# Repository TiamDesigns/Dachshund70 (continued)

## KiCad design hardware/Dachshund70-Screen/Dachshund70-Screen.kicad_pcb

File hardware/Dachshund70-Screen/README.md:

# Dachshund70 screen board

Rev 3.0 (2026-11-17). The board under the 2.7" Sharp memory LCD: the panel's socket, its 5 V supply and the
five layer and battery LEDs. It joins the mainboard with one 12-way flat cable. KiCad 10 project, 2 layers,
0.8 mm FR4, 40.0 × 47.0 mm (x 309 to 349, y 88 to 135 KiCad mm) with R1 corners.

Why a separate board again: the mainboard is held by the switches and moves with the plate's flex, and the
screen is fixed in the case. From mainboard rev 1.3 the mainboard keeps only the keys, the MCU, power and the
connectors, so the same mainboard can go into a cheaper Dachshund70 Lite with no screen and no encoder.

- **Panel:** Sharp LS027B7DH01 (400 × 240, 2.7", 62.8 × 42.82 × 1.64 mm glass, 58.8 × 35.28 mm picture). It
  stands on end beside the knob, so the picture is 240 × 400 in portrait. The firmware build is
  `-DEXTRA_DTC_OVERLAY_FILE=displays/sharp-ls027b7dh01-portrait.overlay`.
- **Every part is on the bottom side.** The top side is a plain ground pour, taped to the back of the panel;
  the LEDs shine up through cut-outs in the board (reverse mount).
- **Same coordinates as the mainboard.** The board is drawn where it sits in the case, so its STEP drops into
  the case model at the same x and y (`python hardware/export_step.py`).

Rev 1.0 (PR #83) drove the 2.13" e-paper; rev 2.0 (PR #84) was this panel without the LEDs; PR #85 moved the
circuit onto the mainboard (rev 1.2), which rev 1.3 undoes.

## Circuit

- **5 V supply.** The panel runs from 5 V. U1, a TI TPS61222 (fixed 5 V boost), makes it from the mainboard's
  3V3, with L1 (4.7 µH), C1 (10 µF in) and C2 (10 µF out).
- **Enable.** U1's EN is VLCD_EN, from the MCU's P0.24 (the overlays' BUSY), with R1 (100 kΩ) pulling it up,
  so the 5 V is on unless the firmware drives it low.
- **Logic.** 3.3 V logic straight into the panel. EXTMODE is tied high, so VCOM follows EXTCOMIN (1 Hz).
- **Sharp's capacitors.** C3 (1 µF), C4 and C5 (100 nF), close to J1.
- **LEDs.** D1 (layer) and D2 to D5 (battery gauge 25/50/75/100%), SK6812MINI-E reverse mount at 7.5 mm pitch
  in a row at y 130.5, x 314.56 to 344.56, each with a 100 nF cap (C6 to C10). They are LEDs 1 to 5 of the
  chain: the data comes from the Caps Lock LED (D2 on the mainboard, LED 0) on the cable as LED_DIN. LED_VDD is
  the mainboard's switched LED supply (its load switch and level buffer stay on the mainboard).

## Cable

Mainboard J4 and this board's J2 are both Hirose FH12-12S-0.5SH(55) (12-way, 0.5 mm). From mainboard rev 1.4 both
sit on the **bottom** of their boards, so JLC can assemble each board from one side. J4 is at the mainboard's right
edge, mouth +x, pads at x 319.45, y 115.15 (pin 1) to 120.65 (pin 12). J2 is 6 mm further right (pads at x 325.45)
at the same y, also mouth +x. The cable leaves J4, loops up and back into J2: a C-shaped loop past the mainboard's
right edge (x 326).

- Use a **0.5 mm pitch, 12-way FFC with contacts on opposite sides at the two ends** (type B): both connectors
  hang under their boards, and the loop turns the cable over. Each conductor keeps its y, so **J2 pin n = J4
  pin n**. The schematics already account for that.
- Length: set it from the case model (gap between the boards plus the loop), and buy a few lengths around it.

| J4 pin (mainboard) | Mainboard net | MCU pin | J2 pin (screen) | Screen net | Panel pin |
| --- | --- | --- | --- | --- | --- |
| 1, 2 | LED_VDD | | 1, 2 | LED_VDD | |
| 3 | GND | | 3 | GND | 9, 10 |
| 4 | LED_DOUT (from D2) | (P0.06 via D2) | 4 | LED_DIN | |
| 5 | GND | | 5 | GND | |
| 6 | DISP_CLK | P0.19 | 6 | SCLK | 1 |
| 7 | DISP_DIN | P0.21 | 7 | SI | 2 |
| 8 | DISP_CS | P0.20 | 8 | SCS (active high) | 3 |
| 9 | DISP_DC | P0.23 | 9 | EXTCOMIN | 4 |
| 10 | DISP_RST | P0.22 | 10 | DISP | 5 |
| 11 | DISP_BUSY | P0.24 | 11 | VLCD_EN (U1's EN) | |
| 12 | +3V3 | | 12 | +3V3 (U1 input) | |

Panel pins 6, 7 (VDDA, VDD) and 8 (EXTMODE) are on +5V. Without the screen board (the Lite), J4 can be left
unfitted: Caps Lock still works, and the firmware is built without a display overlay.

## Geometry

- **J1** (panel socket, FH12-10S) is at (314.6, 110.6), mouth −x, pads at x 316.45 from pin 10 (y 108.35) to
  pin 1 (y 112.85). **J1 pin n = panel pin 11 − n**, assuming the tail folds back under the glass's left edge
  with pin 1 at the top (check it, below).
- The boost (U1, L1, C1, C2, R1) is at the top right, around (330, 96).
- The board stays inside the glass (about x 308 to 351, y 63 to 126) except its LED row, which sits below the
  glass at y 130.5, where the five LEDs light the case's holes.

## Routing

Autorouted with Freerouting 1.9 around a hand-routed LED chain, then hand-fixed (2026-11-18, rev 3.1). The routes
are in `screen_routes.py` (`ROUTES`, `VIAS`), which `gen_screen.py` reads. Power (+5V, +3V3, LED_VDD) and signals
are 0.2 mm (the FH12's 0.5 mm pitch leaves no room for wider tracks at its pads), ground links 0.25 mm; vias
0.6/0.3 mm. The LED chain runs its data on the front between LEDs and LED_VDD as one front row at y 123.8, so the
back stays free around the LEDs' ground pads. There is no ground pour over the mainboard's antenna (rule area
x 318-332, y 120-135, "over the mainboard antenna"): the ground pads of D2, D3, C7, C8 and J2's lower tab reach the
pour on short tracks. There is no stitching grid: eight ground vias, by the connectors, the boost and the LEDs, join
the two pours (and the pour boxed in by J1's tracks); 0.5 mm keep-outs run along the edges and ±2 mm around each LED cut-out
(`Dachshund70-Screen.kicad_dru` allows 0.3 mm from the cut-outs).

## Status

Checked in KiCad only; nothing is ordered, made or fitted. ERC: 0. DRC with schematic parity and every severity:
0 violations, 0 unconnected items.

## Open checks before ordering

- **Panel FPC: pin 1, contact face, pitch, tail position and length**, from Sharp's Figure 8-1 or a panel in
  hand. If pin 1 lands at the bottom of J1, swap `SOCKET` in `gen_screen.py` and reroute.
- **FFC contact sides**: with a type-B cable in a C loop, J4 and J2 (both on the bottom of their boards) must
  each face the cable's contacts.
- **LCSC numbers:** J1/J2 (FH12-10S, FH12-12S), U1 (TPS61222DCKR) and L1 (FNR3015S4R7MT) are still blank.
- **Case:** the board pocket, the cable loop past the mainboard's right edge and the LED holes at x 314.56 +
  7.5 i, y 130.5.

## Regenerating

Run with KiCad 10's Python, from the repo root:

```
"C:/Program Files/KiCad/10.0/bin/python.exe" hardware/Dachshund70-Screen/gen_screen.py
```

This rewrites the schematic and the whole board: placement, the routes from `screen_routes.py`, and the filled
pours. Then check it:

```
kicad-cli pcb drc --schematic-parity --severity-all Dachshund70-Screen.kicad_pcb
kicad-cli sch erc --severity-all Dachshund70-Screen.kicad_sch
```

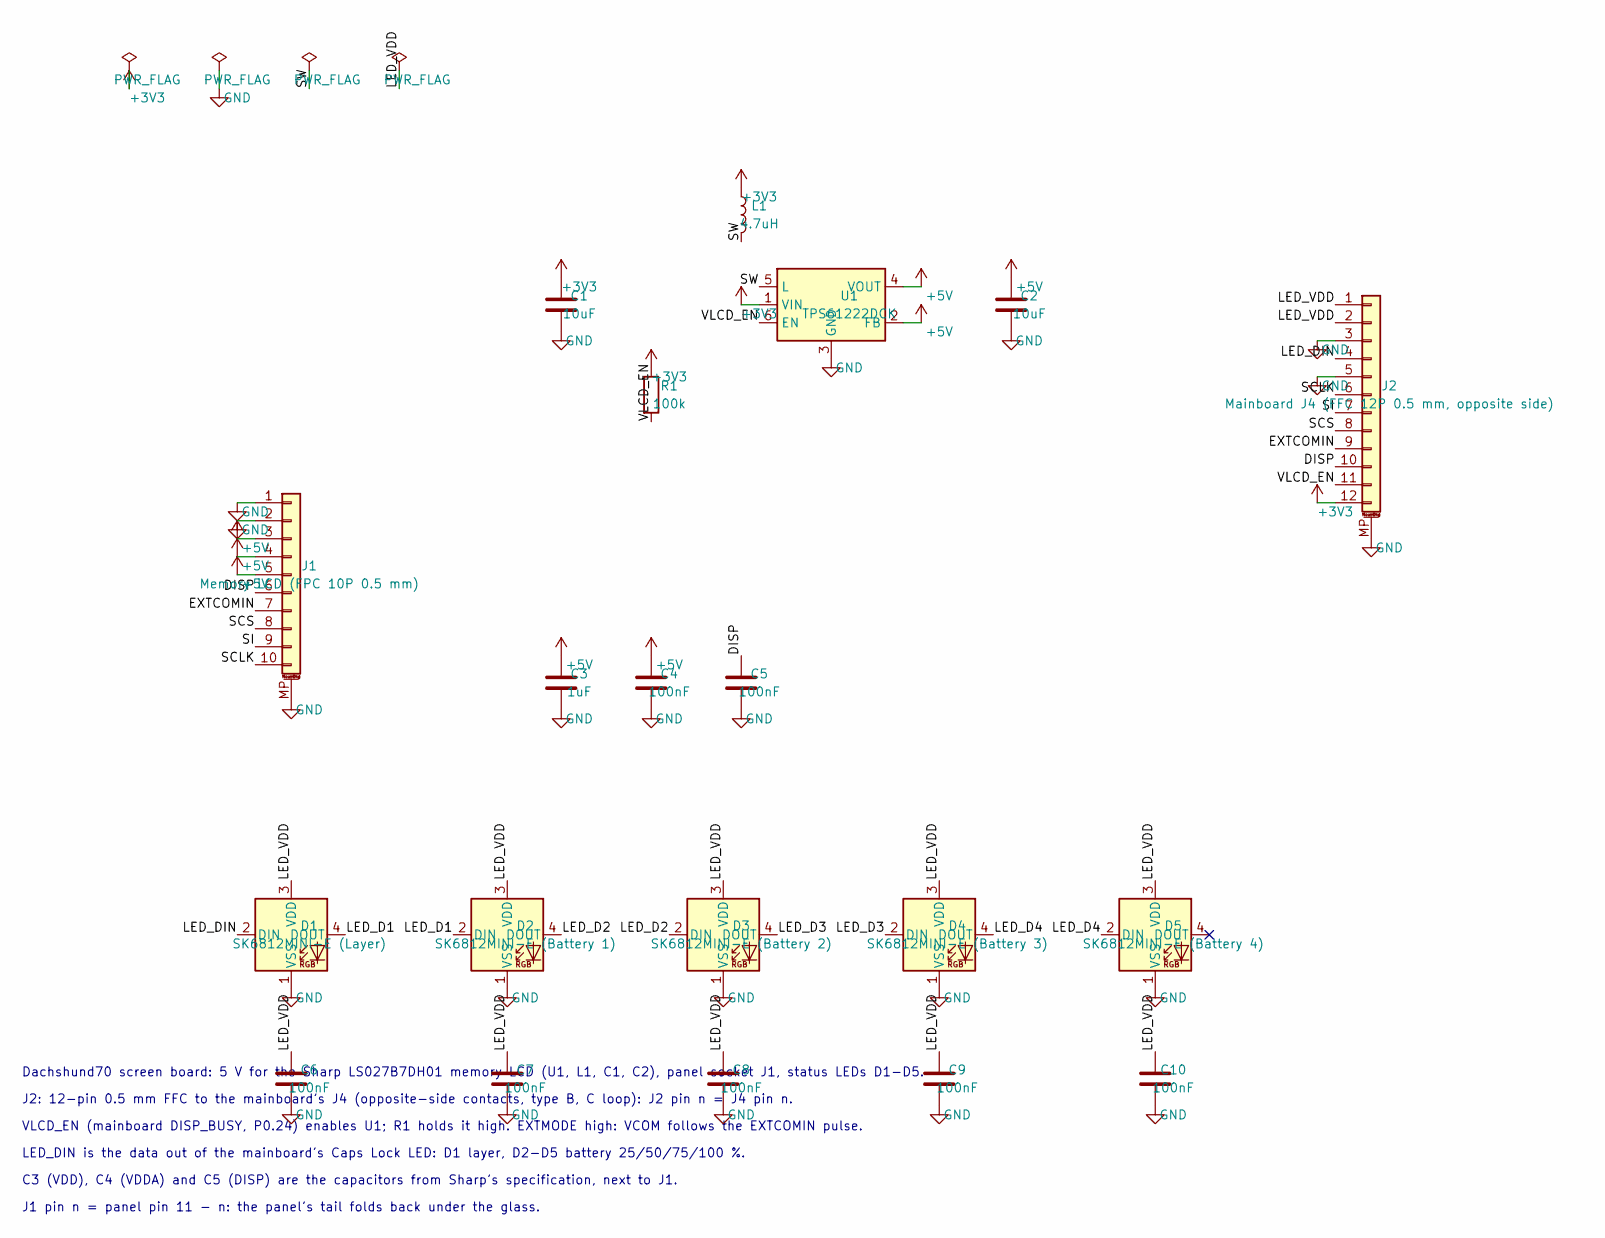
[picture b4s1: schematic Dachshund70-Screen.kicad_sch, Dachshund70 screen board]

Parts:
C1, C2: 10uF; C_0603_1608Metric; MPN Samsung CL10A106KP8NNNC (10 uF, 10 V, X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; LCSC C19702
C3: 1uF; C_0402_1005Metric; MPN Samsung CL05A105KA5NQNC (1 uF, 25 V, X5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; LCSC C52923
C4, C5, C6, C7, C8, C9, C10: 100nF; C_0402_1005Metric; MPN Samsung CL05B104KO5NNNC; LCSC C1525
D1: SK6812MINI-E (Layer); LED_SK6812MINI-E_3.2x2.8mm_P1.5mm_ReverseMount_Cutout3.4; MPN OPSCO SK6812MINI-E; LCSC C5149201
D2: SK6812MINI-E (Battery 1); LED_SK6812MINI-E_3.2x2.8mm_P1.5mm_ReverseMount_Cutout3.4; MPN OPSCO SK6812MINI-E; LCSC C5149201
D3: SK6812MINI-E (Battery 2); LED_SK6812MINI-E_3.2x2.8mm_P1.5mm_ReverseMount_Cutout3.4; MPN OPSCO SK6812MINI-E; LCSC C5149201
D4: SK6812MINI-E (Battery 3); LED_SK6812MINI-E_3.2x2.8mm_P1.5mm_ReverseMount_Cutout3.4; MPN OPSCO SK6812MINI-E; LCSC C5149201
D5: SK6812MINI-E (Battery 4); LED_SK6812MINI-E_3.2x2.8mm_P1.5mm_ReverseMount_Cutout3.4; MPN OPSCO SK6812MINI-E; LCSC C5149201
J1: Memory LCD (FPC 10P 0.5 mm); Hirose_FH12-10S-0.5SH_1x10-1MP_P0.50mm_Horizontal; MPN Hirose FH12-10S-0.5SH(55)
J2: Mainboard J4 (FFC 12P 0.5 mm, opposite side); Hirose_FH12-12S-0.5SH_1x12-1MP_P0.50mm_Horizontal; MPN Hirose FH12-12S-0.5SH(55)
L1: 4.7uH; L_Changjiang_FNR3015S; MPN Changjiang FNR3015S4R7MT (4.7 uH, 3 x 3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
R1: 100k; R_0402_1005Metric; MPN UNI-ROYAL 0402WGF1003TCE; LCSC C25741
U1: TPS61222DCK; SOT-363_SC-70-6; MPN TI TPS61222DCKR (5 V boost)

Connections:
+3V3: C1.1, J2.12, L1.1, R1.1, U1.1 (VIN)
+5V: C2.1, C3.1, C4.1, J1.3, J1.4, J1.5, U1.2 (FB), U1.4 (VOUT)
/DISP: C5.1, J1.6, J2.10
/EXTCOMIN: J1.7, J2.9
/LED_D1: D1.4 (DOUT), D2.2 (DIN)
/LED_D2: D2.4 (DOUT), D3.2 (DIN)
/LED_D3: D3.4 (DOUT), D4.2 (DIN)
/LED_D4: D4.4 (DOUT), D5.2 (DIN)
/LED_DIN: D1.2 (DIN), J2.4
/LED_VDD: C6.1, C7.1, C8.1, C9.1, C10.1, D1.3 (VDD), D2.3 (VDD), D3.3 (VDD), D4.3 (VDD), D5.3 (VDD), J2.1, J2.2
/SCLK: J1.10, J2.6
/SCS: J1.8, J2.8
/SI: J1.9, J2.7
/SW: L1.2, U1.5 (L)
/VLCD_EN: J2.11, R1.2, U1.6 (EN)
GND: C1.2, C2.2, C3.2, C4.2, C5.2, C6.2, C7.2, C8.2, C9.2, C10.2, D1.1 (VSS), D2.1 (VSS), D3.1 (VSS), D4.1 (VSS), D5.1 (VSS), J1.1, J1.2, J1.MP (MountPin), J2.3, J2.5, J2.MP (MountPin), U1.3 (GND)

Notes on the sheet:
Dachshund70 screen board: 5 V for the Sharp LS027B7DH01 memory LCD (U1, L1, C1, C2), panel socket J1, status LEDs D1-D5.
J2: 12-pin 0.5 mm FFC to the mainboard's J4 (opposite-side contacts, type B, C loop): J2 pin n = J4 pin n.
VLCD_EN (mainboard DISP_BUSY, P0.24) enables U1; R1 holds it high. EXTMODE high: VCOM follows the EXTCOMIN pulse.
LED_DIN is the data out of the mainboard's Caps Lock LED: D1 layer, D2-D5 battery 25/50/75/100 %.
C3 (VDD), C4 (VDDA) and C5 (DISP) are the capacitors from Sharp's specification, next to J1.
J1 pin n = panel pin 11 - n: the panel's tail folds back under the glass.

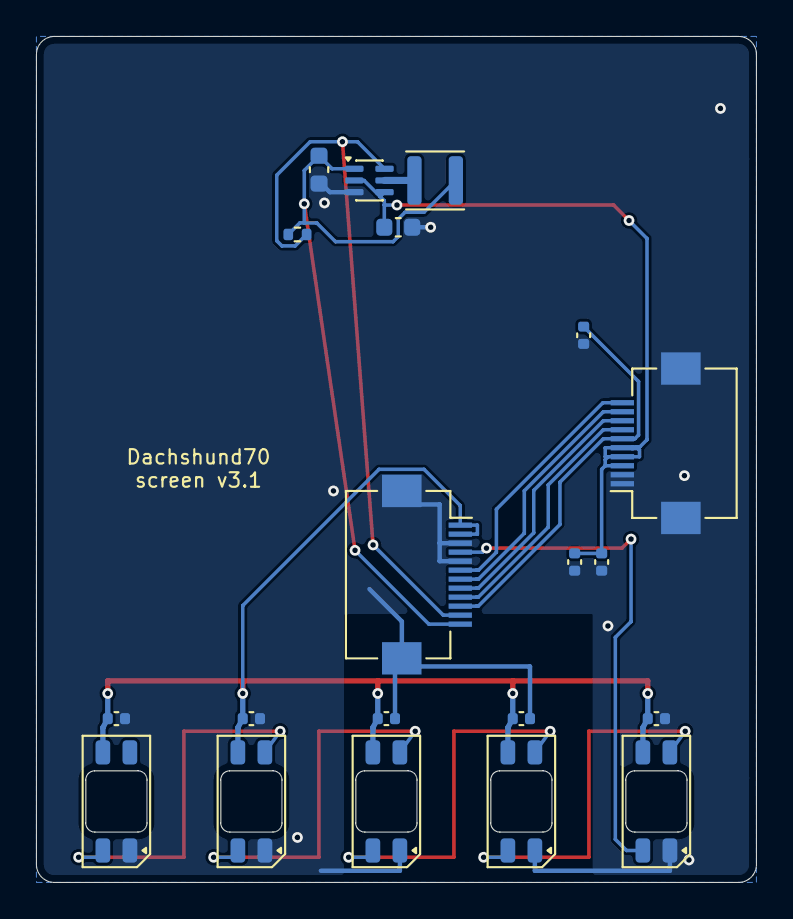
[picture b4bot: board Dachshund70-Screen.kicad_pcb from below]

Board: 2 copper layers, 40.0 x 47.0 mm, 20 parts (20 on the bottom side), 16 nets.

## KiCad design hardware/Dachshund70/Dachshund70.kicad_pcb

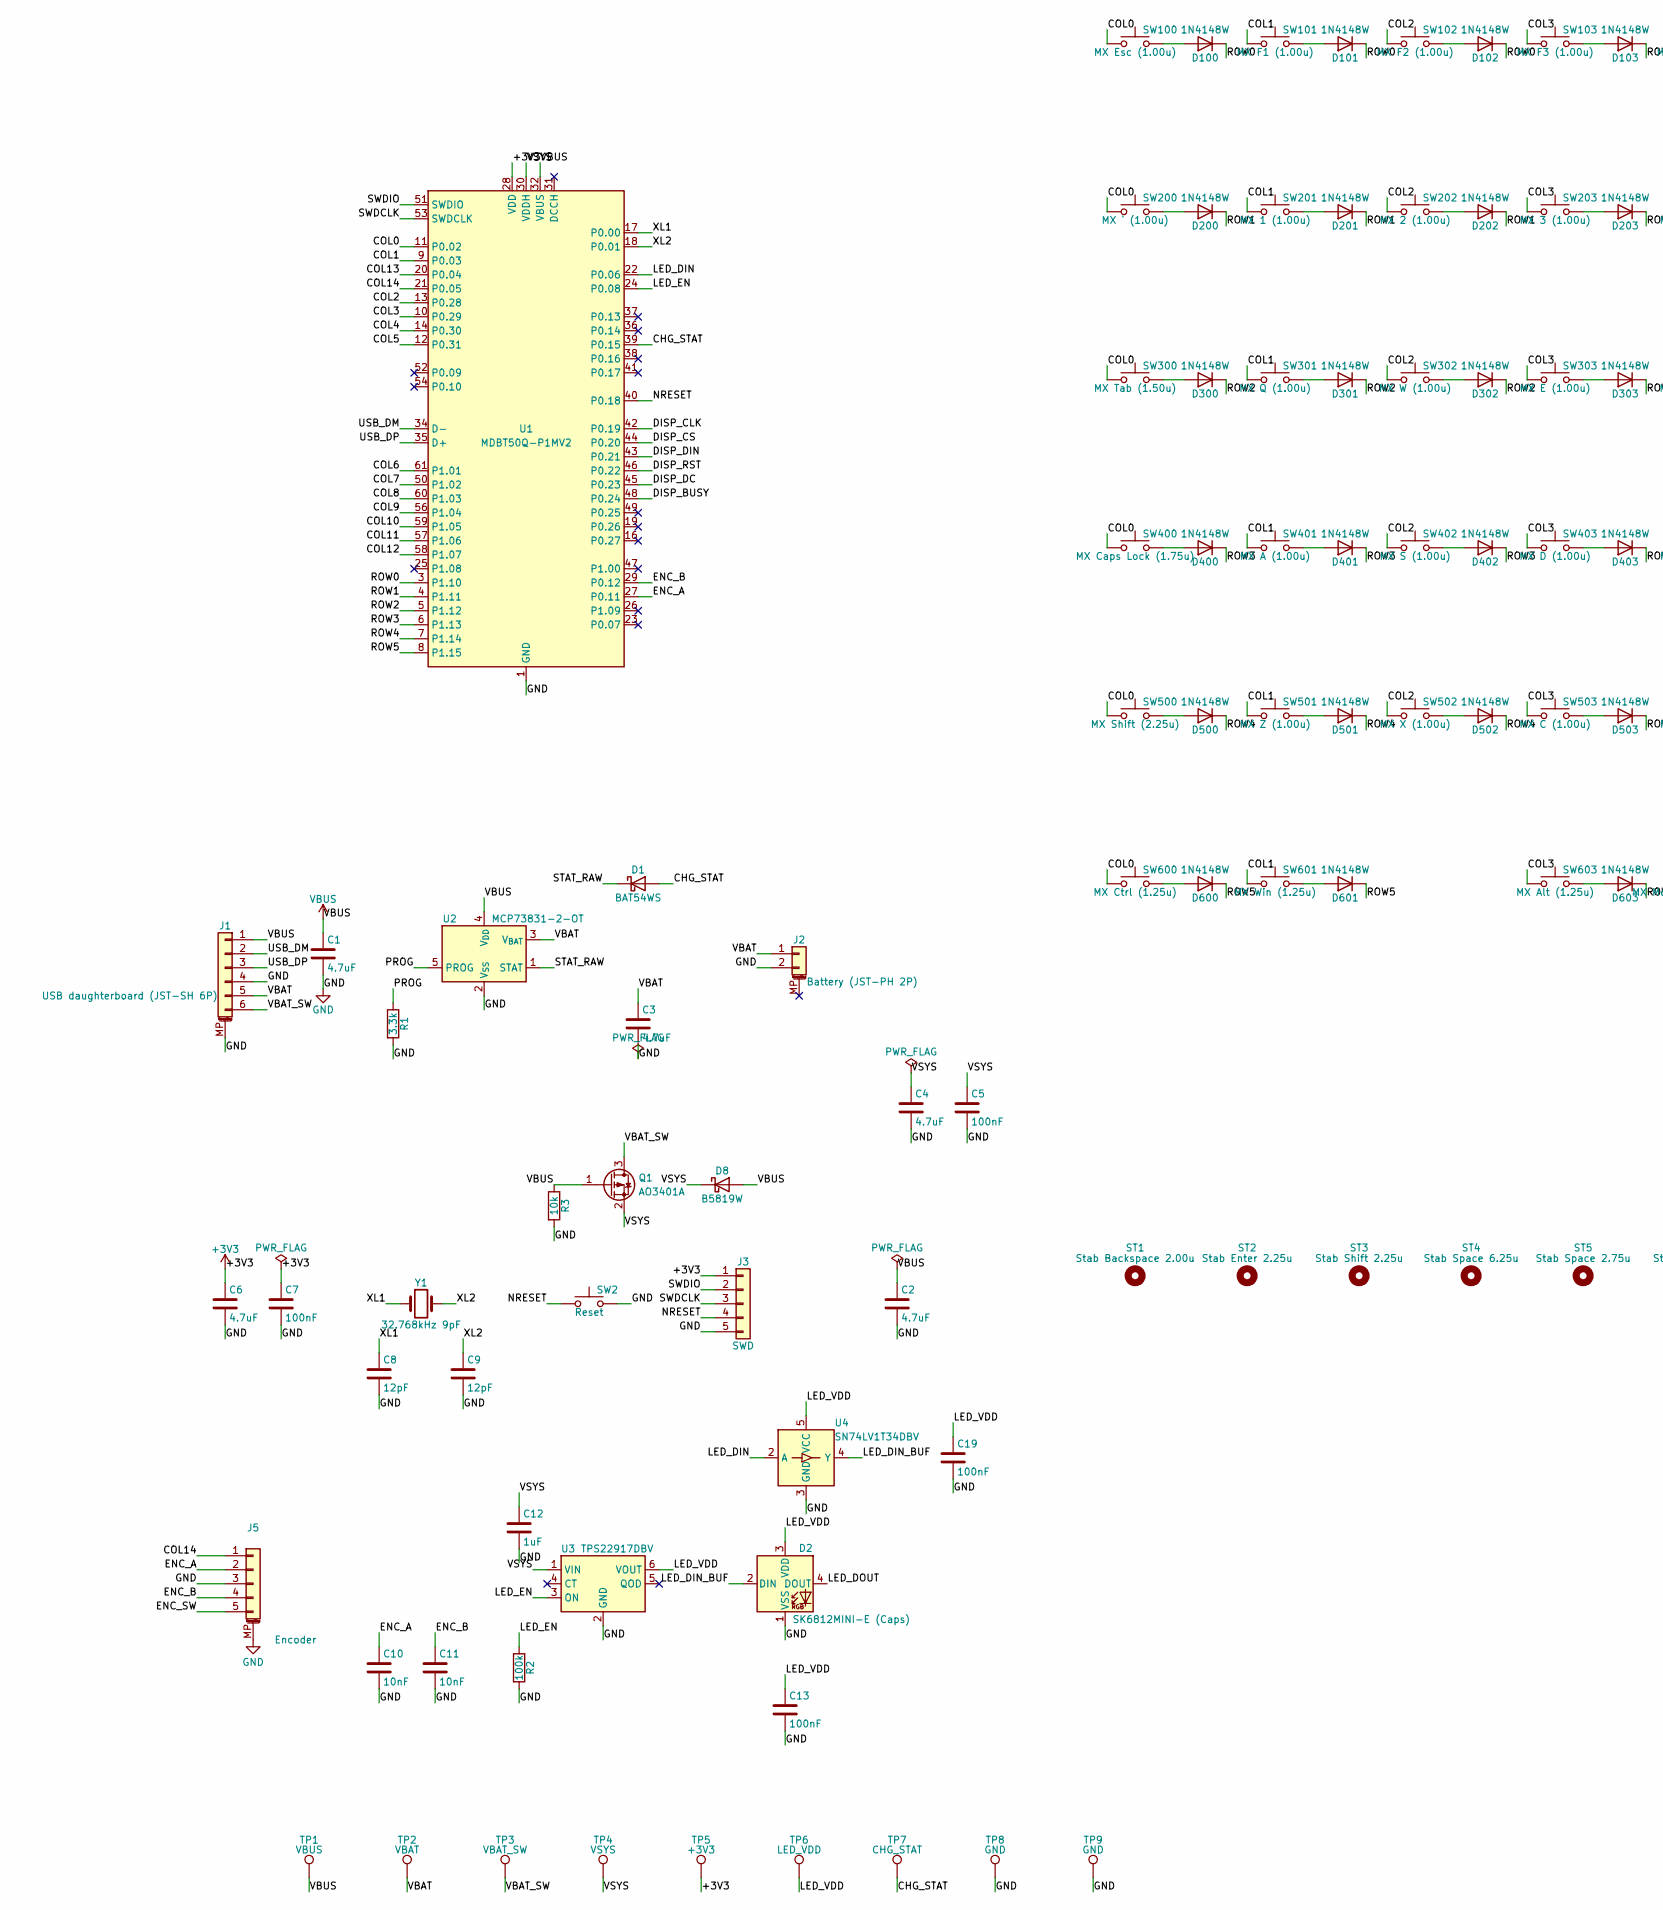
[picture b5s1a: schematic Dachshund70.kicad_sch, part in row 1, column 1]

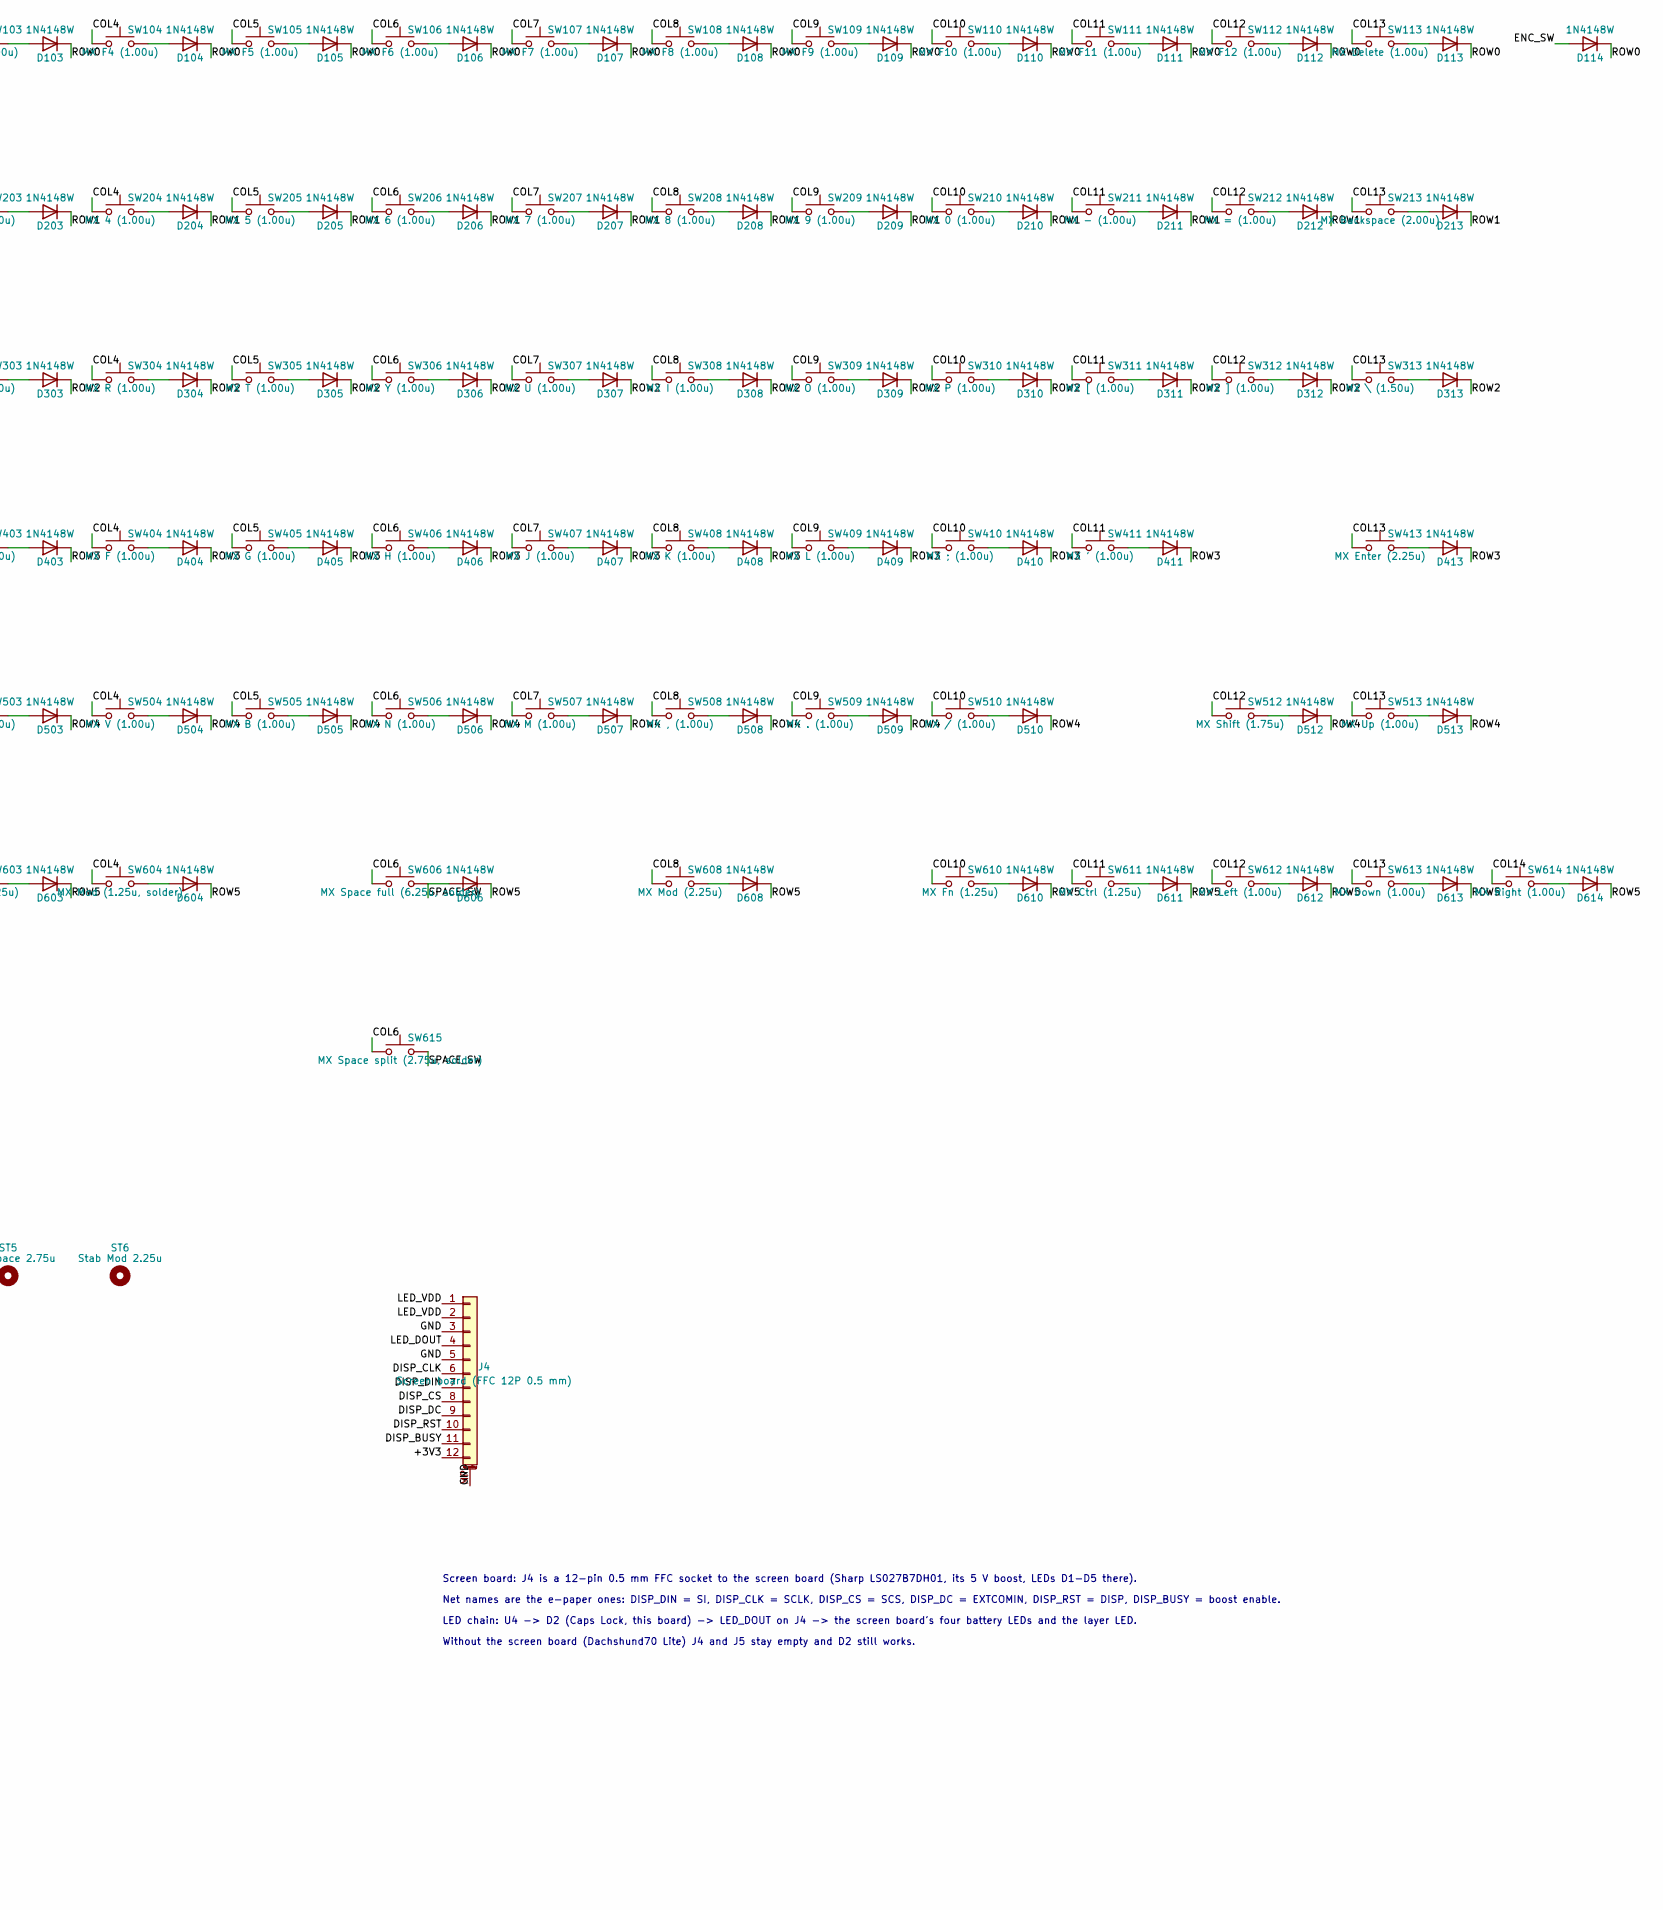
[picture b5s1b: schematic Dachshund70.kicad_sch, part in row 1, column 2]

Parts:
C1, C2, C3, C4, C6: 4.7uF; C_0603_1608Metric; MPN Samsung CL10A475KO8NNNC; LCSC C19666
C5, C7, C13, C19: 100nF; C_0402_1005Metric; MPN Samsung CL05B104KO5NNNC; LCSC C1525
C8, C9: 12pF; C_0402_1005Metric; MPN FH 0402CG120J500NT; LCSC C1547
C10, C11: 10nF; C_0402_1005Metric; MPN Samsung CL05B103KB5NNNC; LCSC C15195
C12: 1uF; C_0402_1005Metric; MPN Samsung CL05A105KA5NQNC; LCSC C52923
D1: BAT54WS; D_SOD-323; MPN CJ BAT54WS; LCSC C2991936
D2: SK6812MINI-E (Caps); LED_SK6812MINI-E_3.2x2.8mm_P1.5mm_ReverseMount_Cutout3.4; MPN OPSCO SK6812MINI-E; LCSC C5149201
D8: B5819W; D_SOD-123; MPN B5819W SL; LCSC C8598
D100, D101, D102, D103, D104, D105, D106, D107, D108, D109, D110, D111, D112, D113, D114, D200, D201, D202, D203, D204, D205, D206, D207, D208, D209, D210, D211, D212, D213, D300, D301, D302, D303, D304, D305, D306, D307, D308, D309, D310, D311, D312, D313, D400, D401, D402, D403, D404, D405, D406, D407, D408, D409, D410, D411, D413, D500, D501, D502, D503, D504, D505, D506, D507, D508, D509, D510, D512, D513, D600, D601, D603, D604, D606, D608, D610, D611, D612, D613, D614: 1N4148W; D_SOD-123; MPN 1N4148W; LCSC C81598
J1: USB daughterboard (JST-SH 6P); JST_SH_SM06B-SRSS-TB_1x06-1MP_P1.00mm_Horizontal; MPN JST SM06B-SRSS-TB(LF)(SN); LCSC C160405
J2: Battery (JST-PH 2P); JST_PH_S2B-PH-SM4-TB_1x02-1MP_P2.00mm_Horizontal; MPN JST S2B-PH-SM4-TB(LF)(SN); LCSC C295747
J3: SWD; PinHeader_1x05_P1.27mm_Vertical; MPN XFCN PZ127V-11-05-H25; LCSC C962329
J4: Screen board (FFC 12P 0.5 mm); Hirose_FH12-12S-0.5SH_1x12-1MP_P0.50mm_Horizontal; MPN Hirose FH12-12S-0.5SH(55)
J5: Encoder; JST_SH_SM05B-SRSS-TB_1x05-1MP_P1.00mm_Horizontal; MPN JST SM05B-SRSS-TB
Q1: AO3401A; SOT-23; MPN AO3401A; LCSC C15127
R1: 3.3k; R_0603_1608Metric; MPN UNI-ROYAL 0603WAF3301T5E; LCSC C22978
R2: 100k; R_0402_1005Metric; MPN UNI-ROYAL 0402WGF1003TCE; LCSC C25741
R3: 10k; R_0603_1608Metric; MPN UNI-ROYAL 0603WAF1002T5E; LCSC C25804
ST1: Stab Backspace 2.00u; Stabilizer_Cherry_MX_2.00u
ST2: Stab Enter 2.25u; Stabilizer_Cherry_MX_2.00u
ST3: Stab Shift 2.25u; Stabilizer_Cherry_MX_2.00u
ST4: Stab Space 6.25u; Stabilizer_Cherry_MX_6.25u
ST5: Stab Space 2.75u; Stabilizer_Cherry_MX_2.00u
ST6: Stab Mod 2.25u; Stabilizer_Cherry_MX_2.00u
SW2: Reset; SW_SPST_TL3342; MPN E-Switch TL3342F160QG; LCSC C2886898
SW100: MX Esc (1.00u); SW_Hotswap_Kailh_MX_1.00u; MPN HanElectricity CPG151101S11-2 (Kailh-pa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; LCSC C49352235
SW101: MX F1 (1.00u); SW_Hotswap_Kailh_MX_1.00u; MPN HanElectricity CPG151101S11-2 (Kailh-pa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; LCSC C49352235
SW102: MX F2 (1.00u); SW_Hotswap_Kailh_MX_1.00u; MPN HanElectricity CPG151101S11-2 (Kailh-pa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; LCSC C49352235
SW103: MX F3 (1.00u); SW_Hotswap_Kailh_MX_1.00u; MPN HanElectricity CPG151101S11-2 (Kailh-pa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; LCSC C49352235
SW104: MX F4 (1.00u); SW_Hotswap_Kailh_MX_1.00u; MPN HanElectricity CPG151101S11-2 (Kailh-pa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; LCSC C49352235
SW105: MX F5 (1.00u); SW_Hotswap_Kailh_MX_1.00u; MPN HanElectricity CPG151101S11-2 (Kailh-pa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; LCSC C49352235
SW106: MX F6 (1.00u); SW_Hotswap_Kailh_MX_1.00u; MPN HanElectricity CPG151101S11-2 (Kailh-pa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; LCSC C49352235
SW107: MX F7 (1.00u); SW_Hotswap_Kailh_MX_1.00u; MPN HanElectricity CPG151101S11-2 (Kailh-pa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; LCSC C49352235
SW108: MX F8 (1.00u); SW_Hotswap_Kailh_MX_1.00u; MPN HanElectricity CPG151101S11-2 (Kailh-pa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; LCSC C49352235
SW109: MX F9 (1.00u); SW_Hotswap_Kailh_MX_1.00u; MPN HanElectricity CPG151101S11-2 (Kailh-pa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; LCSC C49352235
SW110: MX F10 (1.00u); SW_Hotswap_Kailh_MX_1.00u; MPN HanElectricity CPG151101S11-2 (Kailh-pa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; LCSC C49352235
SW111: MX F11 (1.00u); SW_Hotswap_Kailh_MX_1.00u; MPN HanElectricity CPG151101S11-2 (Kailh-pa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; LCSC C49352235
SW112: MX F12 (1.00u); SW_Hotswap_Kailh_MX_1.00u; MPN HanElectricity CPG151101S11-2 (Kailh-pa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; LCSC C49352235
SW113: MX Delete (1.00u); SW_Hotswap_Kailh_MX_1.00u; MPN HanElectricity CPG151101S11-2 (Kailh-pa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; LCSC C49352235
SW200: MX ` (1.00u); SW_Hotswap_Kailh_MX_1.00u; MPN HanElectricity CPG151101S11-2 (Kailh-pa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; LCSC C49352235
SW201: MX 1 (1.00u); SW_Hotswap_Kailh_MX_1.00u; MPN HanElectricity CPG151101S11-2 (Kailh-pa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; LCSC C49352235
SW202: MX 2 (1.00u); SW_Hotswap_Kailh_MX_1.00u; MPN HanElectricity CPG151101S11-2 (Kailh-pa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; LCSC C49352235
SW203: MX 3 (1.00u); SW_Hotswap_Kailh_MX_1.00u; MPN HanElectricity CPG151101S11-2 (Kailh-pa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; LCSC C49352235
SW204: MX 4 (1.00u); SW_Hotswap_Kailh_MX_1.00u; MPN HanElectricity CPG151101S11-2 (Kailh-pa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; LCSC C49352235
SW205: MX 5 (1.00u); SW_Hotswap_Kailh_MX_1.00u; MPN HanElectricity CPG151101S11-2 (Kailh-pa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; LCSC C49352235
SW206: MX 6 (1.00u); SW_Hotswap_Kailh_MX_1.00u; MPN HanElectricity CPG151101S11-2 (Kailh-pa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; LCSC C49352235
SW207: MX 7 (1.00u); SW_Hotswap_Kailh_MX_1.00u; MPN HanElectricity CPG151101S11-2 (Kailh-pa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; LCSC C49352235
SW208: MX 8 (1.00u); SW_Hotswap_Kailh_MX_1.00u; MPN HanElectricity CPG151101S11-2 (Kailh-pa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; LCSC C49352235
SW209: MX 9 (1.00u); SW_Hotswap_Kailh_MX_1.00u; MPN HanElectricity CPG151101S11-2 (Kailh-pa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; LCSC C49352235
SW210: MX 0 (1.00u); SW_Hotswap_Kailh_MX_1.00u; MPN HanElectricity CPG151101S11-2 (Kailh-pa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; LCSC C49352235
SW211: MX - (1.00u); SW_Hotswap_Kailh_MX_1.00u; MPN HanElectricity CPG151101S11-2 (Kailh-pa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; LCSC C49352235
SW212: MX = (1.00u); SW_Hotswap_Kailh_MX_1.00u; MPN HanElectricity CPG151101S11-2 (Kailh-pa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; LCSC C49352235
SW213: MX Backspace (2.00u); SW_Hotswap_Kailh_MX_2.00u; MPN HanElectricity CPG151101S11-2 (Kailh-pa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; LCSC C49352235
SW300: MX Tab (1.50u); SW_Hotswap_Kailh_MX_1.50u; MPN HanElectricity CPG151101S11-2 (Kailh-pa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; LCSC C49352235
SW301: MX Q (1.00u); SW_Hotswap_Kailh_MX_1.00u; MPN HanElectricity CPG151101S11-2 (Kailh-pa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; LCSC C49352235
SW302: MX W (1.00u); SW_Hotswap_Kailh_MX_1.00u; MPN HanElectricity CPG151101S11-2 (Kailh-pa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; LCSC C49352235
SW303: MX E (1.00u); SW_Hotswap_Kailh_MX_1.00u; MPN HanElectricity CPG151101S11-2 (Kailh-pa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; LCSC C49352235
SW304: MX R (1.00u); SW_Hotswap_Kailh_MX_1.00u; MPN HanElectricity CPG151101S11-2 (Kailh-pa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; LCSC C49352235
SW305: MX T (1.00u); SW_Hotswap_Kailh_MX_1.00u; MPN HanElectricity CPG151101S11-2 (Kailh-pa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; LCSC C49352235
SW306: MX Y (1.00u); SW_Hotswap_Kailh_MX_1.00u; MPN HanElectricity CPG151101S11-2 (Kailh-pa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; LCSC C49352235
SW307: MX U (1.00u); SW_Hotswap_Kailh_MX_1.00u; MPN HanElectricity CPG151101S11-2 (Kailh-pa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; LCSC C49352235
SW308: MX I (1.00u); SW_Hotswap_Kailh_MX_1.00u; MPN HanElectricity CPG151101S11-2 (Kailh-pa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; LCSC C49352235
SW309: MX O (1.00u); SW_Hotswap_Kailh_MX_1.00u; MPN HanElectricity CPG151101S11-2 (Kailh-pa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; LCSC C49352235
SW310: MX P (1.00u); SW_Hotswap_Kailh_MX_1.00u; MPN HanElectricity CPG151101S11-2 (Kailh-pa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; LCSC C49352235
SW311: MX [ (1.00u); SW_Hotswap_Kailh_MX_1.00u; MPN HanElectricity CPG151101S11-2 (Kailh-pa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; LCSC C49352235
SW312: MX ] (1.00u); SW_Hotswap_Kailh_MX_1.00u; MPN HanElectricity CPG151101S11-2 (Kailh-pa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; LCSC C49352235
SW313: MX \ (1.50u); SW_Hotswap_Kailh_MX_1.50u; MPN HanElectricity CPG151101S11-2 (Kailh-pa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; LCSC C49352235
SW400: MX Caps Lock (1.75u); SW_Hotswap_Kailh_MX_1.75u; MPN HanElectricity CPG151101S11-2 (Kailh-pa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; LCSC C49352235
SW401: MX A (1.00u); SW_Hotswap_Kailh_MX_1.00u; MPN HanElectricity CPG151101S11-2 (Kailh-pa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; LCSC C49352235
SW402: MX S (1.00u); SW_Hotswap_Kailh_MX_1.00u; MPN HanElectricity CPG151101S11-2 (Kailh-pa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; LCSC C49352235
SW403: MX D (1.00u); SW_Hotswap_Kailh_MX_1.00u; MPN HanElectricity CPG151101S11-2 (Kailh-pa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; LCSC C49352235
SW404: MX F (1.00u); SW_Hotswap_Kailh_MX_1.00u; MPN HanElectricity CPG151101S11-2 (Kailh-pa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; LCSC C49352235
SW405: MX G (1.00u); SW_Hotswap_Kailh_MX_1.00u; MPN HanElectricity CPG151101S11-2 (Kailh-pa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; LCSC C49352235
SW406: MX H (1.00u); SW_Hotswap_Kailh_MX_1.00u; MPN HanElectricity CPG151101S11-2 (Kailh-pa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; LCSC C49352235
SW407: MX J (1.00u); SW_Hotswap_Kailh_MX_1.00u; MPN HanElectricity CPG151101S11-2 (Kailh-pa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; LCSC C49352235
SW408: MX K (1.00u); SW_Hotswap_Kailh_MX_1.00u; MPN HanElectricity CPG151101S11-2 (Kailh-pa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; LCSC C49352235
SW409: MX L (1.00u); SW_Hotswap_Kailh_MX_1.00u; MPN HanElectricity CPG151101S11-2 (Kailh-pa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; LCSC C49352235
SW410: MX ; (1.00u); SW_Hotswap_Kailh_MX_1.00u; MPN HanElectricity CPG151101S11-2 (Kailh-pa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; LCSC C49352235
SW411: MX ' (1.00u); SW_Hotswap_Kailh_MX_1.00u; MPN HanElectricity CPG151101S11-2 (Kailh-pa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; LCSC C49352235
SW413: MX Enter (2.25u); SW_Hotswap_Kailh_MX_2.25u; MPN HanElectricity CPG151101S11-2 (Kailh-pa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; LCSC C49352235
SW500: MX Shift (2.25u); SW_Hotswap_Kailh_MX_2.25u; MPN HanElectricity CPG151101S11-2 (Kailh-pa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; LCSC C49352235
SW501: MX Z (1.00u); SW_Hotswap_Kailh_MX_1.00u; MPN HanElectricity CPG151101S11-2 (Kailh-pa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; LCSC C49352235
SW502: MX X (1.00u); SW_Hotswap_Kailh_MX_1.00u; MPN HanElectricity CPG151101S11-2 (Kailh-pa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; LCSC C49352235
SW503: MX C (1.00u); SW_Hotswap_Kailh_MX_1.00u; MPN HanElectricity CPG151101S11-2 (Kailh-pa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; LCSC C49352235
SW504: MX V (1.00u); SW_Hotswap_Kailh_MX_1.00u; MPN HanElectricity CPG151101S11-2 (Kailh-pa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; LCSC C49352235
SW505: MX B (1.00u); SW_Hotswap_Kailh_MX_1.00u; MPN HanElectricity CPG151101S11-2 (Kailh-pa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; LCSC C49352235
SW506: MX N (1.00u); SW_Hotswap_Kailh_MX_1.00u; MPN HanElectricity CPG151101S11-2 (Kailh-pa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; LCSC C49352235
SW507: MX M (1.00u); SW_Hotswap_Kailh_MX_1.00u; MPN HanElectricity CPG151101S11-2 (Kailh-pa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; LCSC C49352235
SW508: MX , (1.00u); SW_Hotswap_Kailh_MX_1.00u; MPN HanElectricity CPG151101S11-2 (Kailh-pa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; LCSC C49352235
SW509: MX . (1.00u); SW_Hotswap_Kailh_MX_1.00u; MPN HanElectricity CPG151101S11-2 (Kailh-pa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; LCSC C49352235
SW510: MX / (1.00u); SW_Hotswap_Kailh_MX_1.00u; MPN HanElectricity CPG151101S11-2 (Kailh-pa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; LCSC C49352235
SW512: MX Shift (1.75u); SW_Hotswap_Kailh_MX_1.75u; MPN HanElectricity CPG151101S11-2 (Kailh-pa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; LCSC C49352235
SW513: MX Up (1.00u); SW_Hotswap_Kailh_MX_1.00u; MPN HanElectricity CPG151101S11-2 (Kailh-pa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; LCSC C49352235
SW600, SW611: MX Ctrl (1.25u); SW_Hotswap_Kailh_MX_1.25u; MPN HanElectricity CPG151101S11-2 (Kailh-pa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; LCSC C49352235
SW601: MX Win (1.25u); SW_Hotswap_Kailh_MX_1.25u; MPN HanElectricity CPG151101S11-2 (Kailh-pa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; LCSC C49352235
SW603: MX Alt (1.25u); SW_Hotswap_Kailh_MX_1.25u; MPN HanElectricity CPG151101S11-2 (Kailh-pa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; LCSC C49352235
SW604: MX Mod (1.25u, solder); SW_Cherry_MX_1.25u_Plate
SW606: MX Space full (6.25u, solder); SW_Cherry_MX_6.25u_Plate
SW608: MX Mod (2.25u); SW_Hotswap_Kailh_MX_2.25u; MPN HanElectricity CPG151101S11-2 (Kailh-pa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; LCSC C49352235
SW610: MX Fn (1.25u); SW_Hotswap_Kailh_MX_1.25u; MPN HanElectricity CPG151101S11-2 (Kailh-pa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; LCSC C49352235
SW612: MX Left (1.00u); SW_Hotswap_Kailh_MX_1.00u; MPN HanElectricity CPG151101S11-2 (Kailh-pa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; LCSC C49352235
SW613: MX Down (1.00u); SW_Hotswap_Kailh_MX_1.00u; MPN HanElectricity CPG151101S11-2 (Kailh-pa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; LCSC C49352235
SW614: MX Right (1.00u); SW_Hotswap_Kailh_MX_1.00u; MPN HanElectricity CPG151101S11-2 (Kailh-pa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; LCSC C49352235
SW615: MX Space split (2.75u, solder); SW_Cherry_MX_2.75u_Plate
TP1: VBUS; TestPoint_Pad_D1.5mm
TP2: VBAT; TestPoint_Pad_D1.5mm
TP3: VBAT_SW; TestPoint_Pad_D1.5mm
TP4: VSYS; TestPoint_Pad_D1.5mm
TP5: +3V3; TestPoint_Pad_D1.5mm
TP6: LED_VDD; TestPoint_Pad_D1.5mm
TP7: CHG_STAT; TestPoint_Pad_D1.5mm
TP8, TP9: GND; TestPoint_Pad_D1.5mm
U1: MDBT50Q-P1MV2; Raytac_MDBT50Q; MPN Raytac MDBT50Q-P1MV2; LCSC C5119772
U2: MCP73831-2-OT; SOT-23-5; MPN Microchip MCP73831T-2ACI/OT; LCSC C424093
U3: TPS22917DBV; SOT-23-6; MPN TI TPS22917DBVR; LCSC C2681320
U4: SN74LV1T34DBV; SOT-23-5; MPN TI SN74LV1T34DBVR; LCSC C100024
Y1: 32.768kHz 9pF; Crystal_SMD_3215-2Pin_3.2x1.5mm; MPN Epson X1A0000910005 (32.768 kHz, 9 pF); LCSC C255869

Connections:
+3V3: C6.1, C7.1, J3.1, J4.12, TP5.1, U1.28 (VDD)
/CHG_STAT: D1.2 (A), TP7.1, U1.39 (P0.15)
/COL0: SW100.1, SW200.1, SW300.1, SW400.1, SW500.1, SW600.1, U1.11 (P0.02)
/COL1: SW101.1, SW201.1, SW301.1, SW401.1, SW501.1, SW601.1, U1.9 (P0.03)
/COL2: SW102.1, SW202.1, SW302.1, SW402.1, SW502.1, U1.13 (P0.28)
/COL3: SW103.1, SW203.1, SW303.1, SW403.1, SW503.1, SW603.1, U1.10 (P0.29)
/COL4: SW104.1, SW204.1, SW304.1, SW404.1, SW504.1, SW604.1, U1.14 (P0.30)
/COL5: SW105.1, SW205.1, SW305.1, SW405.1, SW505.1, U1.12 (P0.31)
/COL6: SW106.1, SW206.1, SW306.1, SW406.1, SW506.1, SW606.1, SW615.1, U1.61 (P1.01)
/COL7: SW107.1, SW207.1, SW307.1, SW407.1, SW507.1, U1.50 (P1.02)
/COL8: SW108.1, SW208.1, SW308.1, SW408.1, SW508.1, SW608.1, U1.60 (P1.03)
/COL9: SW109.1, SW209.1, SW309.1, SW409.1, SW509.1, U1.56 (P1.04)
/COL10: SW110.1, SW210.1, SW310.1, SW410.1, SW510.1, SW610.1, U1.59 (P1.05)
/COL11: SW111.1, SW211.1, SW311.1, SW411.1, SW611.1, U1.57 (P1.06)
/COL12: SW112.1, SW212.1, SW312.1, SW512.1, SW612.1, U1.58 (P1.07)
/COL13: SW113.1, SW213.1, SW313.1, SW413.1, SW513.1, SW613.1, U1.20 (P0.04)
/COL14: J5.1, SW614.1, U1.21 (P0.05)
/DISP_BUSY: J4.11, U1.48 (P0.24)
/DISP_CLK: J4.6, U1.42 (P0.19)
/DISP_CS: J4.8, U1.44 (P0.20)
/DISP_DC: J4.9, U1.45 (P0.23)
/DISP_DIN: J4.7, U1.43 (P0.21)
/DISP_RST: J4.10, U1.46 (P0.22)
/ENC_A: C10.1, J5.2, U1.27 (P0.11)
/ENC_B: C11.1, J5.4, U1.29 (P0.12)
/ENC_SW: D114.2 (A), J5.5
/LED_DIN: U1.22 (P0.06), U4.2 (A)
/LED_DIN_BUF: D2.2 (DIN), U4.4 (Y)
/LED_DOUT: D2.4 (DOUT), J4.4
/LED_EN: R2.1, U1.24 (P0.08), U3.3 (ON)
/LED_VDD: C13.1, C19.1, D2.3 (VDD), J4.1, J4.2, TP6.1, U3.6 (VOUT), U4.5 (VCC)
/NRESET: J3.4, SW2.1, U1.40 (P0.18)
/PROG: R1.1, U2.5 (PROG)
/ROW0: D100.1 (K), D101.1 (K), D102.1 (K), D103.1 (K), D104.1 (K), D105.1 (K), D106.1 (K), D107.1 (K), D108.1 (K), D109.1 (K), D110.1 (K), D111.1 (K), D112.1 (K), D113.1 (K), D114.1 (K), U1.3 (P1.10)
/ROW1: D200.1 (K), D201.1 (K), D202.1 (K), D203.1 (K), D204.1 (K), D205.1 (K), D206.1 (K), D207.1 (K), D208.1 (K), D209.1 (K), D210.1 (K), D211.1 (K), D212.1 (K), D213.1 (K), U1.4 (P1.11)
/ROW2: D300.1 (K), D301.1 (K), D302.1 (K), D303.1 (K), D304.1 (K), D305.1 (K), D306.1 (K), D307.1 (K), D308.1 (K), D309.1 (K), D310.1 (K), D311.1 (K), D312.1 (K), D313.1 (K), U1.5 (P1.12)
/ROW3: D400.1 (K), D401.1 (K), D402.1 (K), D403.1 (K), D404.1 (K), D405.1 (K), D406.1 (K), D407.1 (K), D408.1 (K), D409.1 (K), D410.1 (K), D411.1 (K), D413.1 (K), U1.6 (P1.13)
/ROW4: D500.1 (K), D501.1 (K), D502.1 (K), D503.1 (K), D504.1 (K), D505.1 (K), D506.1 (K), D507.1 (K), D508.1 (K), D509.1 (K), D510.1 (K), D512.1 (K), D513.1 (K), U1.7 (P1.14)
/ROW5: D600.1 (K), D601.1 (K), D603.1 (K), D604.1 (K), D606.1 (K), D608.1 (K), D610.1 (K), D611.1 (K), D612.1 (K), D613.1 (K), D614.1 (K), U1.8 (P1.15)
/SPACE_SW: D606.2 (A), SW606.2, SW615.2
/STAT_RAW: D1.1 (K), U2.1 (STAT)
/SWDCLK: J3.3, U1.53 (SWDCLK)
/SWDIO: J3.2, U1.51 (SWDIO)
/USB_DM: J1.2, U1.34 (D-)
/USB_DP: J1.3, U1.35 (D+)
/VBAT: C3.1, J1.5, J2.1, TP2.1, U2.3 (V_{BAT})
/VBAT_SW: J1.6, Q1.3 (D), TP3.1
/VSYS: C4.1, C5.1, C12.1, D8.1 (K), Q1.2 (S), TP4.1, U1.30 (VDDH), U3.1 (VIN)
/XL1: C8.1, U1.17 (P0.00), Y1.1
/XL2: C9.1, U1.18 (P0.01), Y1.2
GND: C1.2, C2.2, C3.2, C4.2, C5.2, C6.2, C7.2, C8.2, C9.2, C10.2, C11.2, C12.2, C13.2, C19.2, D2.1 (VSS), J1.4, J1.MP (MountPin), J2.2, J3.5, J4.3, J4.5, J4.MP (MountPin), J5.3, J5.MP (MountPin), R1.2, R2.2, R3.2, SW2.2, TP8.1, TP9.1, U1.1 (GND), U1.2 (GND), U1.15 (GND), U1.33 (GND), U1.55 (GND), U2.2 (V_{SS}), U3.2 (GND), U4.3 (GND)
unnamed: D100.2 (A), SW100.2
unnamed: D101.2 (A), SW101.2
unnamed: D102.2 (A), SW102.2
unnamed: D103.2 (A), SW103.2
unnamed: D104.2 (A), SW104.2
unnamed: D105.2 (A), SW105.2
unnamed: D106.2 (A), SW106.2
unnamed: D107.2 (A), SW107.2
unnamed: D108.2 (A), SW108.2
unnamed: D109.2 (A), SW109.2
unnamed: D110.2 (A), SW110.2
unnamed: D111.2 (A), SW111.2
unnamed: D112.2 (A), SW112.2
unnamed: D113.2 (A), SW113.2
unnamed: D200.2 (A), SW200.2
unnamed: D201.2 (A), SW201.2
unnamed: D202.2 (A), SW202.2
unnamed: D203.2 (A), SW203.2
unnamed: D204.2 (A), SW204.2
unnamed: D205.2 (A), SW205.2
unnamed: D206.2 (A), SW206.2
unnamed: D207.2 (A), SW207.2
unnamed: D208.2 (A), SW208.2
unnamed: D209.2 (A), SW209.2
unnamed: D210.2 (A), SW210.2
unnamed: D211.2 (A), SW211.2
unnamed: D212.2 (A), SW212.2
unnamed: D213.2 (A), SW213.2
unnamed: D300.2 (A), SW300.2
unnamed: D301.2 (A), SW301.2
unnamed: D302.2 (A), SW302.2
unnamed: D303.2 (A), SW303.2
unnamed: D304.2 (A), SW304.2
unnamed: D305.2 (A), SW305.2
unnamed: D306.2 (A), SW306.2
unnamed: D307.2 (A), SW307.2
unnamed: D308.2 (A), SW308.2
unnamed: D309.2 (A), SW309.2
unnamed: D310.2 (A), SW310.2
unnamed: D311.2 (A), SW311.2
unnamed: D312.2 (A), SW312.2
unnamed: D313.2 (A), SW313.2
unnamed: D400.2 (A), SW400.2
unnamed: D401.2 (A), SW401.2
unnamed: D402.2 (A), SW402.2
unnamed: D403.2 (A), SW403.2
unnamed: D404.2 (A), SW404.2
unnamed: D405.2 (A), SW405.2
unnamed: D406.2 (A), SW406.2
unnamed: D407.2 (A), SW407.2
unnamed: D408.2 (A), SW408.2
unnamed: D409.2 (A), SW409.2
unnamed: D410.2 (A), SW410.2
unnamed: D411.2 (A), SW411.2
unnamed: D413.2 (A), SW413.2
unnamed: D500.2 (A), SW500.2
unnamed: D501.2 (A), SW501.2
unnamed: D502.2 (A), SW502.2
unnamed: D503.2 (A), SW503.2
unnamed: D504.2 (A), SW504.2
unnamed: D505.2 (A), SW505.2
unnamed: D506.2 (A), SW506.2
unnamed: D507.2 (A), SW507.2
unnamed: D508.2 (A), SW508.2
unnamed: D509.2 (A), SW509.2
unnamed: D510.2 (A), SW510.2
unnamed: D512.2 (A), SW512.2
unnamed: D513.2 (A), SW513.2
unnamed: D600.2 (A), SW600.2
unnamed: D601.2 (A), SW601.2
unnamed: D603.2 (A), SW603.2
unnamed: D604.2 (A), SW604.2
unnamed: D608.2 (A), SW608.2
unnamed: D610.2 (A), SW610.2
unnamed: D611.2 (A), SW611.2
unnamed: D612.2 (A), SW612.2
unnamed: D613.2 (A), SW613.2
unnamed: D614.2 (A), SW614.2
VBUS: C1.1, C2.1, D8.2 (A), J1.1, Q1.1 (G), R3.1, TP1.1, U1.32 (VBUS), U2.4 (V_{DD})

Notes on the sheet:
Without the screen board (Dachshund70 Lite) J4 and J5 stay empty and D2 still works.
Screen board: J4 is a 12-pin 0.5 mm FFC socket to the screen board (Sharp LS027B7DH01, its 5 V boost, LEDs D1-D5 there).
Net names are the e-paper ones: DISP_DIN = SI, DISP_CLK = SCLK, DISP_CS = SCS, DISP_DC = EXTCOMIN, DISP_RST = DISP, DISP_BUSY = boost enable.
LED chain: U4 -> D2 (Caps Lock, this board) -> LED_DOUT on J4 -> the screen board's four battery LEDs and the layer LED.
